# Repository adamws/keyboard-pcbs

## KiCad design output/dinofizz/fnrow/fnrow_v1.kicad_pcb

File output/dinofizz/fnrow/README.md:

## dinofizz/fnrow/fnrow_v1

[layout](fnrow_v1-kle.json) - [PCB](fnrow_v1.kicad_pcb)

{:loading="lazy"}

[Open in keyboard-layout-editor](http://www.keyboard-layout-editor.com/##@@_c=#777777;&=0,0&_x:1&c=#cccccc;&=0,1&=0,2&=0,3&=0,4&_x:0.5&c=#aaaaaa;&=0,5&=0,6&=1,0&=1,1&_x:0.5&c=#cccccc;&=1,2&=1,3&=1,4&=1,5)

{:loading="lazy"}

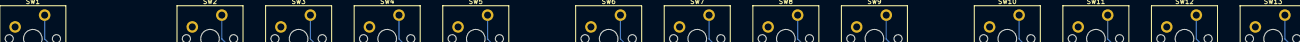
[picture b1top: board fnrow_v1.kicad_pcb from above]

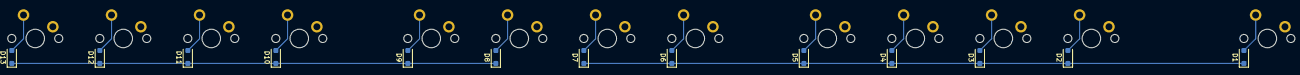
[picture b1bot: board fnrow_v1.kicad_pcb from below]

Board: 2 copper layers, 26 parts (13 on the bottom side), 21 nets.

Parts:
D1, D2, D3, D4, D5, D6, D7, D8, D9, D10, D11, D12, D13: D_SOD-123F
SW1, SW2, SW3, SW4, SW5, SW6, SW7, SW8, SW9, SW10, SW11, SW12, SW13: SW_Cherry_MX_PCB_1.00u

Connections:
COL0: SW1.1, SW8.1
COL1: SW2.1, SW9.1
COL2: SW3.1, SW10.1
COL3: SW4.1, SW11.1
COL4: SW5.1, SW12.1
COL5: SW6.1, SW13.1
unnamed: D1.2, SW1.2
unnamed: D2.2, SW2.2
unnamed: D3.2, SW3.2
unnamed: D4.2, SW4.2
unnamed: D5.2, SW5.2
unnamed: D6.2, SW6.2
unnamed: D7.2, SW7.2
unnamed: D8.2, SW8.2
unnamed: D9.2, SW9.2
unnamed: D10.2, SW10.2
unnamed: D11.2, SW11.2
unnamed: D12.2, SW12.2
unnamed: D13.2, SW13.2
ROW0: D1.1, D2.1, D3.1, D4.1, D5.1, D6.1, D7.1
ROW1: D8.1, D9.1, D10.1, D11.1, D12.1, D13.1

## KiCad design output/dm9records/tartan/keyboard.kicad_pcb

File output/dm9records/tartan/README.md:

## dm9records/tartan/keyboard

[layout](keyboard-kle.json) - [PCB](keyboard.kicad_pcb)

{:loading="lazy"}

[Open in keyboard-layout-editor](http://www.keyboard-layout-editor.com/##@@_x:2.5&c=#777777;&=0,0&_c=#cccccc;&=0,1&=0,2&=0,3&=0,4&=0,5&=0,6&=0,7&=0,8&=0,9&=0,10&=0,11&=0,12&_c=#aaaaaa&w:2;&=4,9%0A%0A%0A0,0;&@_x:2.5&w:1.5;&=1,0&_c=#cccccc;&=1,1&=1,2&=1,3&=1,4&=1,5&=1,6&=1,7&=1,8&=1,9&=1,10&=1,11&=1,12&_w:1.5;&=4,11%0A%0A%0A1,0;&@_x:2.5&c=#aaaaaa&w:1.75;&=2,0&_c=#cccccc;&=2,1&=2,2&=2,3&=2,4&=2,5&=2,6&=2,7&=2,8&=2,9&=2,10&=2,11&_c=#777777&w:2.25;&=2,12%0A%0A%0A1,0;&@_x:2.5&c=#aaaaaa&w:2.25;&=3,0%0A%0A%0A3,0&_c=#cccccc;&=3,2&=3,3&=3,4&=3,5&=3,6&=3,7&=3,8&=3,9&=3,10&=3,11&_c=#aaaaaa&w:2.75;&=3,12%0A%0A%0A2,0;&@_x:2.5&w:1.25;&=4,0&_w:1.25;&=4,1&_w:1.25;&=4,2&_c=#cccccc&w:6.25;&=4,3&_c=#aaaaaa&w:1.25;&=4,4&_w:1.25;&=4,5&_w:1.25;&=4,6&_w:1.25;&=4,7;&@_x:17.75&y:-5&c=#cccccc;&=4,11%0A%0A%0A0,1&_c=#aaaaaa;&=4,9%0A%0A%0A0,1;&@_x:18.75&c=#777777&w:1.25&h:2&w2:1.5&h2:1&x2:-0.25;&=2,12%0A%0A%0A1,1;&@_x:17.75&c=#cccccc;&=4,11%0A%0A%0A1,1;&@_c=#aaaaaa&w:1.25;&=3,0%0A%0A%0A3,1&_c=#cccccc;&=3,1%0A%0A%0A3,1&_x:15.5&c=#aaaaaa&w:1.75&w2:1;&=3,12%0A%0A%0A2,1&_c=#cccccc;&=4,12%0A%0A%0A2,1)

{:loading="lazy"}

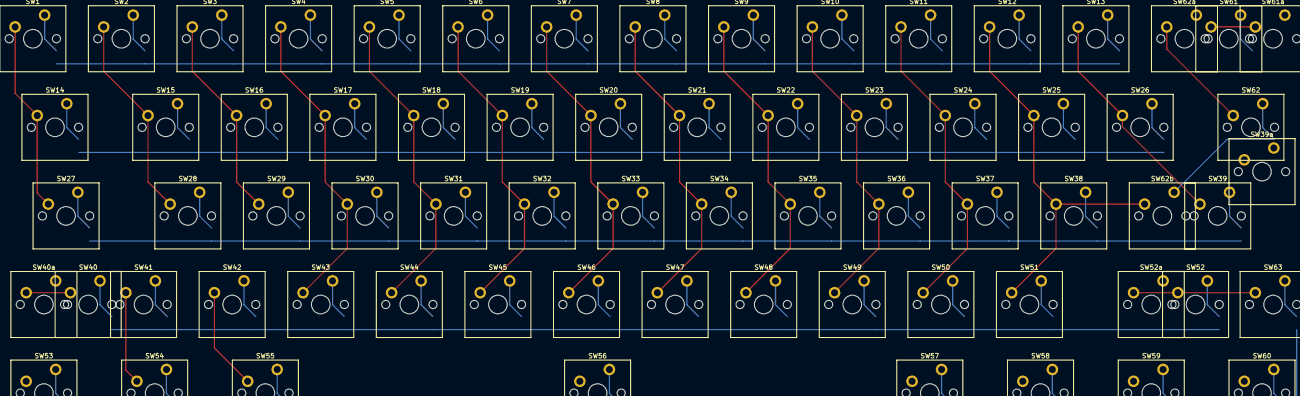
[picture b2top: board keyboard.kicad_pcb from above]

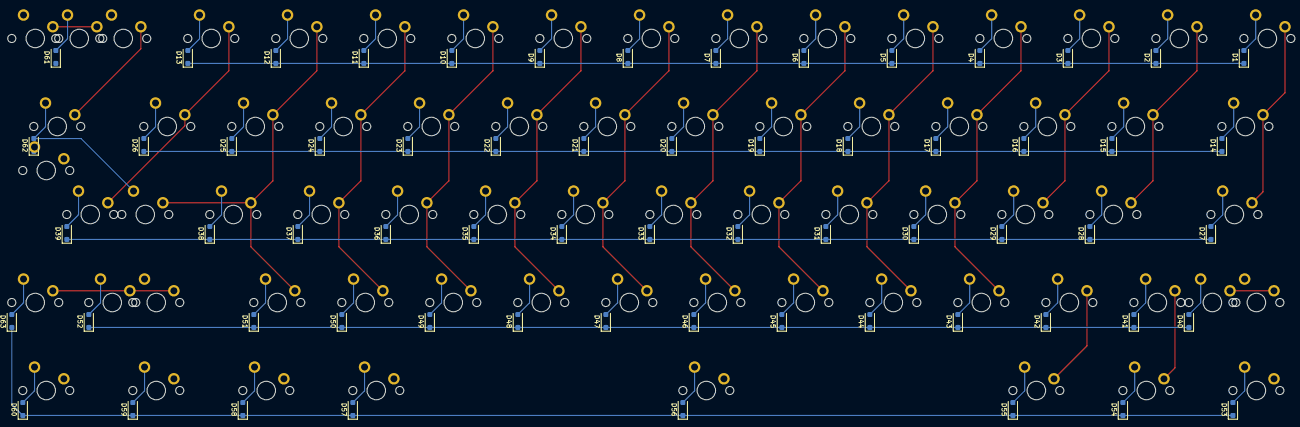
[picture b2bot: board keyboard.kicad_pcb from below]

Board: 2 copper layers, 132 parts (63 on the bottom side), 81 nets.

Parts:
D1, D2, D3, D4, D5, D6, D7, D8, D9, D10, D11, D12, D13, D14, D15, D16, D17, D18, D19, D20, D21, D22, D23, D24, D25, D26, D27, D28, D29, D30, D31, D32, D33, D34, D35, D36, D37, D38, D39, D40, D41, D42, D43, D44, D45, D46, D47, D48, D49, D50, D51, D52, D53, D54, D55, D56, D57, D58, D59, D60, D61, D62, D63: D_SOD-123F
SW1, SW2, SW3, SW4, SW5, SW6, SW7, SW8, SW9, SW10, SW11, SW12, SW13, SW14, SW15, SW16, SW17, SW18, SW19, SW20, SW21, SW22, SW23, SW24, SW25, SW26, SW27, SW28, SW29, SW30, SW31, SW32, SW33, SW34, SW35, SW36, SW37, SW38, SW39, SW39a, SW40, SW40a, SW41, SW42, SW43, SW44, SW45, SW46, SW47, SW48, SW49, SW50, SW51, SW52, SW52a, SW53, SW54, SW55, SW56, SW57, SW58, SW59, SW60, SW61, SW61a, SW62, SW62a, SW62b, SW63: SW_Cherry_MX_PCB_1.00u

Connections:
COL0: SW1.1, SW14.1, SW27.1, SW40.1, SW40a.1, SW53.1
COL1: SW2.1, SW15.1, SW28.1, SW41.1, SW54.1
COL2: SW3.1, SW16.1, SW29.1, SW42.1, SW55.1
COL3: SW4.1, SW17.1, SW30.1, SW43.1, SW56.1
COL4: SW5.1, SW18.1, SW31.1, SW44.1, SW57.1
COL5: SW6.1, SW19.1, SW32.1, SW45.1, SW58.1
COL6: SW7.1, SW20.1, SW33.1, SW46.1, SW59.1
COL7: SW8.1, SW21.1, SW34.1, SW47.1, SW60.1
COL8: SW9.1, SW22.1, SW35.1, SW48.1
COL9: SW10.1, SW23.1, SW36.1, SW49.1, SW61.1, SW61a.1
COL10: SW11.1, SW24.1, SW37.1, SW50.1
COL11: SW12.1, SW25.1, SW38.1, SW51.1, SW62.1, SW62a.1, SW62b.1
COL12: SW13.1, SW26.1, SW39.1, SW39a.1, SW52.1, SW52a.1, SW63.1
unnamed: D1.2, SW1.2
unnamed: D2.2, SW2.2
unnamed: D3.2, SW3.2
unnamed: D4.2, SW4.2
unnamed: D5.2, SW5.2
unnamed: D6.2, SW6.2
unnamed: D7.2, SW7.2
unnamed: D8.2, SW8.2
unnamed: D9.2, SW9.2
unnamed: D10.2, SW10.2
unnamed: D11.2, SW11.2
unnamed: D12.2, SW12.2
unnamed: D13.2, SW13.2
unnamed: D14.2, SW14.2
unnamed: D15.2, SW15.2
unnamed: D16.2, SW16.2
unnamed: D17.2, SW17.2
unnamed: D18.2, SW18.2
unnamed: D19.2, SW19.2
unnamed: D20.2, SW20.2
unnamed: D21.2, SW21.2
unnamed: D22.2, SW22.2
unnamed: D23.2, SW23.2
unnamed: D24.2, SW24.2
unnamed: D25.2, SW25.2
unnamed: D26.2, SW26.2
unnamed: D27.2, SW27.2
unnamed: D28.2, SW28.2
unnamed: D29.2, SW29.2
unnamed: D30.2, SW30.2
unnamed: D31.2, SW31.2
unnamed: D32.2, SW32.2
unnamed: D33.2, SW33.2
unnamed: D34.2, SW34.2
unnamed: D35.2, SW35.2
unnamed: D36.2, SW36.2
unnamed: D37.2, SW37.2
unnamed: D38.2, SW38.2
unnamed: D39.2, SW39.2, SW39a.2
unnamed: D40.2, SW40.2, SW40a.2
unnamed: D41.2, SW41.2
unnamed: D42.2, SW42.2
unnamed: D43.2, SW43.2
unnamed: D44.2, SW44.2
unnamed: D45.2, SW45.2
unnamed: D46.2, SW46.2
unnamed: D47.2, SW47.2
unnamed: D48.2, SW48.2
unnamed: D49.2, SW49.2
unnamed: D50.2, SW50.2
unnamed: D51.2, SW51.2
unnamed: D52.2, SW52.2, SW52a.2
unnamed: D53.2, SW53.2
unnamed: D54.2, SW54.2
unnamed: D55.2, SW55.2
unnamed: D56.2, SW56.2
unnamed: D57.2, SW57.2
unnamed: D58.2, SW58.2
unnamed: D59.2, SW59.2
unnamed: D60.2, SW60.2
unnamed: D61.2, SW61.2, SW61a.2
unnamed: D62.2, SW62.2, SW62a.2, SW62b.2
unnamed: D63.2, SW63.2
ROW0: D1.1, D2.1, D3.1, D4.1, D5.1, D6.1, D7.1, D8.1, D9.1, D10.1, D11.1, D12.1, D13.1
ROW1: D14.1, D15.1, D16.1, D17.1, D18.1, D19.1, D20.1, D21.1, D22.1, D23.1, D24.1, D25.1, D26.1
ROW2: D27.1, D28.1, D29.1, D30.1, D31.1, D32.1, D33.1, D34.1, D35.1, D36.1, D37.1, D38.1, D39.1
ROW3: D40.1, D41.1, D42.1, D43.1, D44.1, D45.1, D46.1, D47.1, D48.1, D49.1, D50.1, D51.1, D52.1
ROW4: D53.1, D54.1, D55.1, D56.1, D57.1, D58.1, D59.1, D60.1, D61.1, D62.1, D63.1

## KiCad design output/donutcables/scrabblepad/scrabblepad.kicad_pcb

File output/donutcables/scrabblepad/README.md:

## donutcables/scrabblepad

[layout](scrabblepad-kle.json) - [PCB](scrabblepad.kicad_pcb)

{:loading="lazy"}

[Open in keyboard-layout-editor](http://www.keyboard-layout-editor.com/##@@=0,0&=0,1&=0,2&=0,3&=0,4&=0,5&=0,6&=0,7&=0,8&=0,9&=0,10&=0,11&=0,12&=0,13&=0,14;&@=1,0&=1,1&=1,2&=1,3&=1,4&=1,5&=1,6&=1,7&=1,8&=1,9&=1,10&=1,11&=1,12&=1,13&=1,14;&@=2,0&=2,1&=2,2&=2,3&=2,4&=2,5&=2,6&=2,7&=2,8&=2,9&=2,10&=2,11&=2,12&=2,13&=2,14;&@=3,0&=3,1&=3,2&=3,3&=3,4&=3,5&=3,6&=3,7&=3,8&=3,9&=3,10&=3,11&=3,12&=3,13&=3,14;&@=4,0&=4,1&=4,2&=4,3&=4,4&=4,5&=4,6&=4,7&=4,8&=4,9&=4,10&=4,11&=4,12&=4,13&=4,14;&@=5,0&=5,1&=5,2&=5,3&=5,4&=5,5&=5,6&=5,7&=5,8&=5,9&=5,10&=5,11&=5,12&=5,13&=5,14;&@=6,0&=6,1&=6,2&=6,3&=6,4&=6,5&=6,6&=6,7&=6,8&=6,9&=6,10&=6,11&=6,12&=6,13&=6,14;&@=7,0&=7,1&=7,2&=7,3&=7,4&=7,5&=7,6&=7,7&=7,8&=7,9&=7,10&=7,11&=7,12&=7,13&=7,14;&@=8,0&=8,1&=8,2&=8,3&=8,4&=8,5&=8,6&=8,7&=8,8&=8,9&=8,10&=8,11&=8,12&=8,13&=8,14;&@=9,0&=9,1&=9,2&=9,3&=9,4&=9,5&=9,6&=9,7&=9,8&=9,9&=9,10&=9,11&=9,12&=9,13&=9,14;&@=10,0&=10,1&=10,2&=10,3&=10,4&=10,5&=10,6&=10,7&=10,8&=10,9&=10,10&=10,11&=10,12&=10,13&=10,14;&@=11,0&=11,1&=11,2&=11,3&=11,4&=11,5&=11,6&=11,7&=11,8&=11,9&=11,10&=11,11&=11,12&=11,13&=11,14;&@=12,0&=12,1&=12,2&=12,3&=12,4&=12,5&=12,6&=12,7&=12,8&=12,9&=12,10&=12,11&=12,12&=12,13&=12,14;&@=13,0&=13,1&=13,2&=13,3&=13,4&=13,5&=13,6&=13,7&=13,8&=13,9&=13,10&=13,11&=13,12&=13,13&=13,14;&@=14,0&=14,1&=14,2&=14,3&=14,4&=14,5&=14,6&=14,7&=14,8&=14,9&=14,10&=14,11&=14,12&=14,13&=14,14)

{:loading="lazy"}

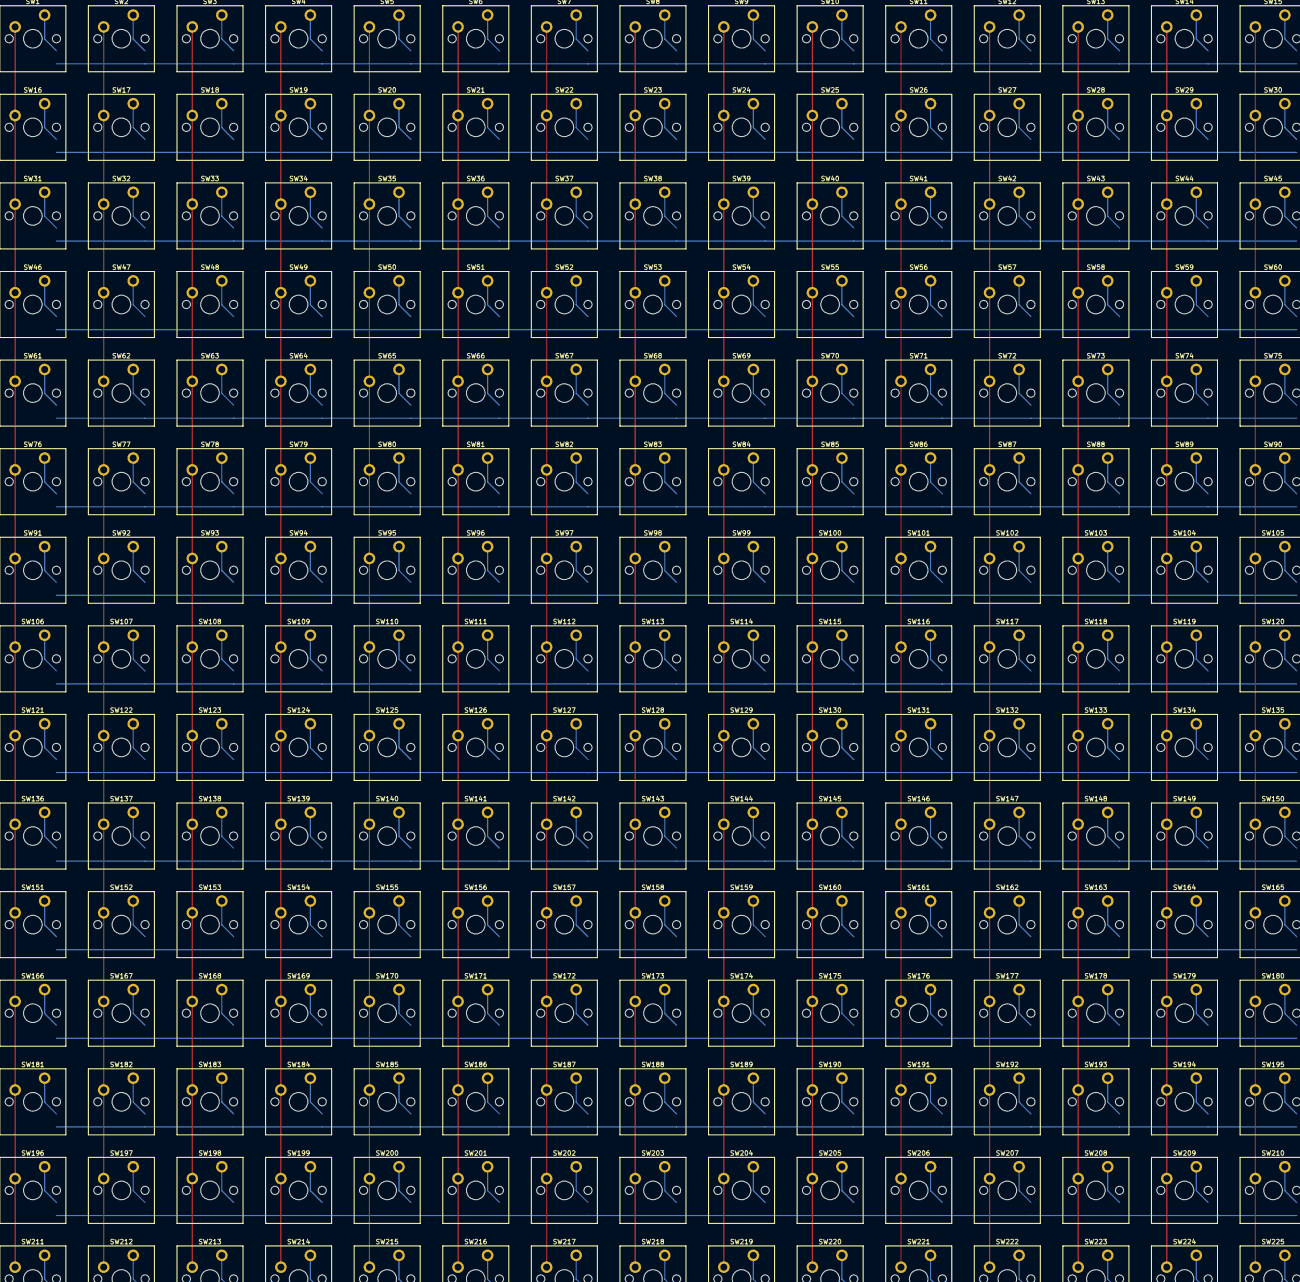
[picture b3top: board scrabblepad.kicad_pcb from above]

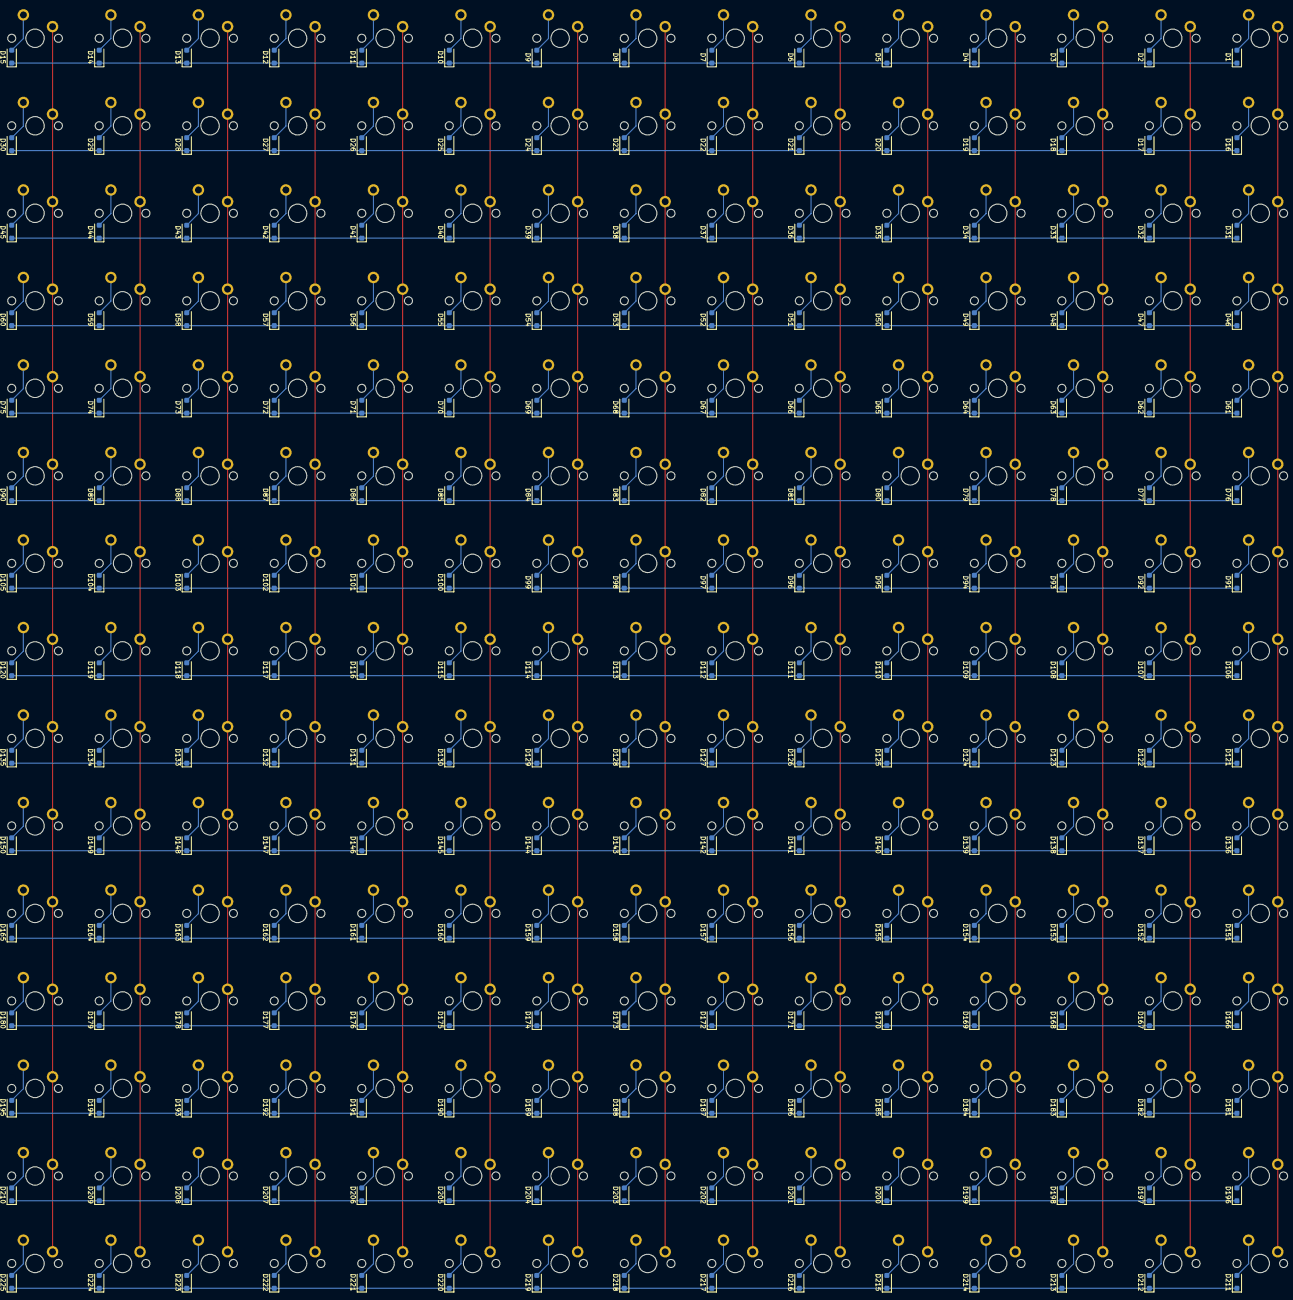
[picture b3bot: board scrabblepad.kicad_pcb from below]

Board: 2 copper layers, 450 parts (225 on the bottom side), 255 nets.

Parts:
D1, D2, D3, D4, D5, D6, D7, D8, D9, D10, D11, D12, D13, D14, D15, D16, D17, D18, D19, D20, D21, D22, D23, D24, D25, D26, D27, D28, D29, D30, D31, D32, D33, D34, D35, D36, D37, D38, D39, D40, D41, D42, D43, D44, D45, D46, D47, D48, D49, D50, D51, D52, D53, D54, D55, D56, D57, D58, D59, D60, D61, D62, D63, D64, D65, D66, D67, D68, D69, D70, D71, D72, D73, D74, D75, D76, D77, D78, D79, D80, D81, D82, D83, D84, D85, D86, D87, D88, D89, D90, D91, D92, D93, D94, D95, D96, D97, D98, D99, D100, D101, D102, D103, D104, D105, D106, D107, D108, D109, D110, D111, D112, D113, D114, D115, D116, D117, D118, D119, D120, D121, D122, D123, D124, D125, D126, D127, D128, D129, D130, D131, D132, D133, D134, D135, D136, D137, D138, D139, D140, D141, D142, D143, D144, D145, D146, D147, D148, D149, D150, D151, D152, D153, D154, D155, D156, D157, D158, D159, D160, D161, D162, D163, D164, D165, D166, D167, D168, D169, D170, D171, D172, D173, D174, D175, D176, D177, D178, D179, D180, D181, D182, D183, D184, D185, D186, D187, D188, D189, D190, D191, D192, D193, D194, D195, D196, D197, D198, D199, D200, D201, D202, D203, D204, D205, D206, D207, D208, D209, D210, D211, D212, D213, D214, D215, D216, D217, D218, D219, D220, D221, D222, D223, D224, D225: D_SOD-123F
SW1, SW2, SW3, SW4, SW5, SW6, SW7, SW8, SW9, SW10, SW11, SW12, SW13, SW14, SW15, SW16, SW17, SW18, SW19, SW20, SW21, SW22, SW23, SW24, SW25, SW26, SW27, SW28, SW29, SW30, SW31, SW32, SW33, SW34, SW35, SW36, SW37, SW38, SW39, SW40, SW41, SW42, SW43, SW44, SW45, SW46, SW47, SW48, SW49, SW50, SW51, SW52, SW53, SW54, SW55, SW56, SW57, SW58, SW59, SW60, SW61, SW62, SW63, SW64, SW65, SW66, SW67, SW68, SW69, SW70, SW71, SW72, SW73, SW74, SW75, SW76, SW77, SW78, SW79, SW80, SW81, SW82, SW83, SW84, SW85, SW86, SW87, SW88, SW89, SW90, SW91, SW92, SW93, SW94, SW95, SW96, SW97, SW98, SW99, SW100, SW101, SW102, SW103, SW104, SW105, SW106, SW107, SW108, SW109, SW110, SW111, SW112, SW113, SW114, SW115, SW116, SW117, SW118, SW119, SW120, SW121, SW122, SW123, SW124, SW125, SW126, SW127, SW128, SW129, SW130, SW131, SW132, SW133, SW134, SW135, SW136, SW137, SW138, SW139, SW140, SW141, SW142, SW143, SW144, SW145, SW146, SW147, SW148, SW149, SW150, SW151, SW152, SW153, SW154, SW155, SW156, SW157, SW158, SW159, SW160, SW161, SW162, SW163, SW164, SW165, SW166, SW167, SW168, SW169, SW170, SW171, SW172, SW173, SW174, SW175, SW176, SW177, SW178, SW179, SW180, SW181, SW182, SW183, SW184, SW185, SW186, SW187, SW188, SW189, SW190, SW191, SW192, SW193, SW194, SW195, SW196, SW197, SW198, SW199, SW200, SW201, SW202, SW203, SW204, SW205, SW206, SW207, SW208, SW209, SW210, SW211, SW212, SW213, SW214, SW215, SW216, SW217, SW218, SW219, SW220, SW221, SW222, SW223, SW224, SW225: SW_Cherry_MX_PCB_1.00u

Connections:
COL0: SW1.1, SW16.1, SW31.1, SW46.1, SW61.1, SW76.1, SW91.1, SW106.1, SW121.1, SW136.1, SW151.1, SW166.1, SW181.1, SW196.1, SW211.1
COL1: SW2.1, SW17.1, SW32.1, SW47.1, SW62.1, SW77.1, SW92.1, SW107.1, SW122.1, SW137.1, SW152.1, SW167.1, SW182.1, SW197.1, SW212.1
COL2: SW3.1, SW18.1, SW33.1, SW48.1, SW63.1, SW78.1, SW93.1, SW108.1, SW123.1, SW138.1, SW153.1, SW168.1, SW183.1, SW198.1, SW213.1
COL3: SW4.1, SW19.1, SW34.1, SW49.1, SW64.1, SW79.1, SW94.1, SW109.1, SW124.1, SW139.1, SW154.1, SW169.1, SW184.1, SW199.1, SW214.1
COL4: SW5.1, SW20.1, SW35.1, SW50.1, SW65.1, SW80.1, SW95.1, SW110.1, SW125.1, SW140.1, SW155.1, SW170.1, SW185.1, SW200.1, SW215.1
COL5: SW6.1, SW21.1, SW36.1, SW51.1, SW66.1, SW81.1, SW96.1, SW111.1, SW126.1, SW141.1, SW156.1, SW171.1, SW186.1, SW201.1, SW216.1
COL6: SW7.1, SW22.1, SW37.1, SW52.1, SW67.1, SW82.1, SW97.1, SW112.1, SW127.1, SW142.1, SW157.1, SW172.1, SW187.1, SW202.1, SW217.1
COL7: SW8.1, SW23.1, SW38.1, SW53.1, SW68.1, SW83.1, SW98.1, SW113.1, SW128.1, SW143.1, SW158.1, SW173.1, SW188.1, SW203.1, SW218.1
COL8: SW9.1, SW24.1, SW39.1, SW54.1, SW69.1, SW84.1, SW99.1, SW114.1, SW129.1, SW144.1, SW159.1, SW174.1, SW189.1, SW204.1, SW219.1
COL9: SW10.1, SW25.1, SW40.1, SW55.1, SW70.1, SW85.1, SW100.1, SW115.1, SW130.1, SW145.1, SW160.1, SW175.1, SW190.1, SW205.1, SW220.1
COL10: SW11.1, SW26.1, SW41.1, SW56.1, SW71.1, SW86.1, SW101.1, SW116.1, SW131.1, SW146.1, SW161.1, SW176.1, SW191.1, SW206.1, SW221.1
COL11: SW12.1, SW27.1, SW42.1, SW57.1, SW72.1, SW87.1, SW102.1, SW117.1, SW132.1, SW147.1, SW162.1, SW177.1, SW192.1, SW207.1, SW222.1
COL12: SW13.1, SW28.1, SW43.1, SW58.1, SW73.1, SW88.1, SW103.1, SW118.1, SW133.1, SW148.1, SW163.1, SW178.1, SW193.1, SW208.1, SW223.1
COL13: SW14.1, SW29.1, SW44.1, SW59.1, SW74.1, SW89.1, SW104.1, SW119.1, SW134.1, SW149.1, SW164.1, SW179.1, SW194.1, SW209.1, SW224.1
COL14: SW15.1, SW30.1, SW45.1, SW60.1, SW75.1, SW90.1, SW105.1, SW120.1, SW135.1, SW150.1, SW165.1, SW180.1, SW195.1, SW210.1, SW225.1
unnamed: D1.2, SW1.2
unnamed: D2.2, SW2.2
unnamed: D3.2, SW3.2
unnamed: D4.2, SW4.2
unnamed: D5.2, SW5.2
unnamed: D6.2, SW6.2
unnamed: D7.2, SW7.2
unnamed: D8.2, SW8.2
unnamed: D9.2, SW9.2
unnamed: D10.2, SW10.2
unnamed: D11.2, SW11.2
unnamed: D12.2, SW12.2
unnamed: D13.2, SW13.2
unnamed: D14.2, SW14.2
unnamed: D15.2, SW15.2
unnamed: D16.2, SW16.2
unnamed: D17.2, SW17.2
unnamed: D18.2, SW18.2
unnamed: D19.2, SW19.2
unnamed: D20.2, SW20.2
unnamed: D21.2, SW21.2
unnamed: D22.2, SW22.2
unnamed: D23.2, SW23.2
unnamed: D24.2, SW24.2
unnamed: D25.2, SW25.2
unnamed: D26.2, SW26.2
unnamed: D27.2, SW27.2
unnamed: D28.2, SW28.2
unnamed: D29.2, SW29.2
unnamed: D30.2, SW30.2
unnamed: D31.2, SW31.2
unnamed: D32.2, SW32.2
unnamed: D33.2, SW33.2
unnamed: D34.2, SW34.2
unnamed: D35.2, SW35.2
unnamed: D36.2, SW36.2
unnamed: D37.2, SW37.2
unnamed: D38.2, SW38.2
unnamed: D39.2, SW39.2
unnamed: D40.2, SW40.2
unnamed: D41.2, SW41.2
unnamed: D42.2, SW42.2
unnamed: D43.2, SW43.2
unnamed: D44.2, SW44.2
unnamed: D45.2, SW45.2
unnamed: D46.2, SW46.2
unnamed: D47.2, SW47.2
unnamed: D48.2, SW48.2
unnamed: D49.2, SW49.2
unnamed: D50.2, SW50.2
unnamed: D51.2, SW51.2
unnamed: D52.2, SW52.2
unnamed: D53.2, SW53.2
unnamed: D54.2, SW54.2
unnamed: D55.2, SW55.2
unnamed: D56.2, SW56.2
unnamed: D57.2, SW57.2
unnamed: D58.2, SW58.2
unnamed: D59.2, SW59.2
unnamed: D60.2, SW60.2
unnamed: D61.2, SW61.2
unnamed: D62.2, SW62.2
unnamed: D63.2, SW63.2
unnamed: D64.2, SW64.2
unnamed: D65.2, SW65.2
unnamed: D66.2, SW66.2
unnamed: D67.2, SW67.2
unnamed: D68.2, SW68.2
unnamed: D69.2, SW69.2
unnamed: D70.2, SW70.2
unnamed: D71.2, SW71.2
unnamed: D72.2, SW72.2
unnamed: D73.2, SW73.2
unnamed: D74.2, SW74.2
unnamed: D75.2, SW75.2
unnamed: D76.2, SW76.2
unnamed: D77.2, SW77.2
unnamed: D78.2, SW78.2
unnamed: D79.2, SW79.2
unnamed: D80.2, SW80.2
unnamed: D81.2, SW81.2
unnamed: D82.2, SW82.2
unnamed: D83.2, SW83.2
unnamed: D84.2, SW84.2
unnamed: D85.2, SW85.2
unnamed: D86.2, SW86.2
unnamed: D87.2, SW87.2
unnamed: D88.2, SW88.2
unnamed: D89.2, SW89.2
unnamed: D90.2, SW90.2
unnamed: D91.2, SW91.2
unnamed: D92.2, SW92.2
unnamed: D93.2, SW93.2
unnamed: D94.2, SW94.2
unnamed: D95.2, SW95.2
unnamed: D96.2, SW96.2
unnamed: D97.2, SW97.2
unnamed: D98.2, SW98.2
unnamed: D99.2, SW99.2
unnamed: D100.2, SW100.2
unnamed: D101.2, SW101.2
unnamed: D102.2, SW102.2
unnamed: D103.2, SW103.2
unnamed: D104.2, SW104.2
unnamed: D105.2, SW105.2
unnamed: D106.2, SW106.2
unnamed: D107.2, SW107.2
unnamed: D108.2, SW108.2
unnamed: D109.2, SW109.2
unnamed: D110.2, SW110.2
unnamed: D111.2, SW111.2
unnamed: D112.2, SW112.2
unnamed: D113.2, SW113.2
unnamed: D114.2, SW114.2
unnamed: D115.2, SW115.2
unnamed: D116.2, SW116.2
unnamed: D117.2, SW117.2
unnamed: D118.2, SW118.2
unnamed: D119.2, SW119.2
unnamed: D120.2, SW120.2
unnamed: D121.2, SW121.2
unnamed: D122.2, SW122.2
unnamed: D123.2, SW123.2
unnamed: D124.2, SW124.2
unnamed: D125.2, SW125.2
unnamed: D126.2, SW126.2
unnamed: D127.2, SW127.2
unnamed: D128.2, SW128.2
unnamed: D129.2, SW129.2
unnamed: D130.2, SW130.2
unnamed: D131.2, SW131.2
unnamed: D132.2, SW132.2
unnamed: D133.2, SW133.2
unnamed: D134.2, SW134.2
unnamed: D135.2, SW135.2
unnamed: D136.2, SW136.2
unnamed: D137.2, SW137.2
unnamed: D138.2, SW138.2
unnamed: D139.2, SW139.2
unnamed: D140.2, SW140.2
unnamed: D141.2, SW141.2
unnamed: D142.2, SW142.2
unnamed: D143.2, SW143.2
unnamed: D144.2, SW144.2
unnamed: D145.2, SW145.2
unnamed: D146.2, SW146.2
unnamed: D147.2, SW147.2
unnamed: D148.2, SW148.2
unnamed: D149.2, SW149.2
unnamed: D150.2, SW150.2
unnamed: D151.2, SW151.2
unnamed: D152.2, SW152.2
unnamed: D153.2, SW153.2
unnamed: D154.2, SW154.2
unnamed: D155.2, SW155.2
unnamed: D156.2, SW156.2
unnamed: D157.2, SW157.2
unnamed: D158.2, SW158.2
unnamed: D159.2, SW159.2
unnamed: D160.2, SW160.2
unnamed: D161.2, SW161.2
unnamed: D162.2, SW162.2
unnamed: D163.2, SW163.2
unnamed: D164.2, SW164.2
unnamed: D165.2, SW165.2
unnamed: D166.2, SW166.2
unnamed: D167.2, SW167.2
unnamed: D168.2, SW168.2
unnamed: D169.2, SW169.2
unnamed: D170.2, SW170.2
unnamed: D171.2, SW171.2
unnamed: D172.2, SW172.2
unnamed: D173.2, SW173.2
unnamed: D174.2, SW174.2
unnamed: D175.2, SW175.2
unnamed: D176.2, SW176.2
unnamed: D177.2, SW177.2
unnamed: D178.2, SW178.2
unnamed: D179.2, SW179.2
unnamed: D180.2, SW180.2
unnamed: D181.2, SW181.2
unnamed: D182.2, SW182.2
unnamed: D183.2, SW183.2
unnamed: D184.2, SW184.2
unnamed: D185.2, SW185.2
unnamed: D186.2, SW186.2
unnamed: D187.2, SW187.2
unnamed: D188.2, SW188.2
unnamed: D189.2, SW189.2
unnamed: D190.2, SW190.2
unnamed: D191.2, SW191.2
unnamed: D192.2, SW192.2
unnamed: D193.2, SW193.2
unnamed: D194.2, SW194.2
unnamed: D195.2, SW195.2
unnamed: D196.2, SW196.2
unnamed: D197.2, SW197.2
unnamed: D198.2, SW198.2
unnamed: D199.2, SW199.2
unnamed: D200.2, SW200.2
unnamed: D201.2, SW201.2
unnamed: D202.2, SW202.2
unnamed: D203.2, SW203.2
unnamed: D204.2, SW204.2
unnamed: D205.2, SW205.2
unnamed: D206.2, SW206.2
unnamed: D207.2, SW207.2
unnamed: D208.2, SW208.2
unnamed: D209.2, SW209.2
unnamed: D210.2, SW210.2
unnamed: D211.2, SW211.2
unnamed: D212.2, SW212.2
unnamed: D213.2, SW213.2
unnamed: D214.2, SW214.2
unnamed: D215.2, SW215.2
unnamed: D216.2, SW216.2
unnamed: D217.2, SW217.2
unnamed: D218.2, SW218.2
unnamed: D219.2, SW219.2
unnamed: D220.2, SW220.2
unnamed: D221.2, SW221.2
unnamed: D222.2, SW222.2
unnamed: D223.2, SW223.2
unnamed: D224.2, SW224.2
unnamed: D225.2, SW225.2
ROW0: D1.1, D2.1, D3.1, D4.1, D5.1, D6.1, D7.1, D8.1, D9.1, D10.1, D11.1, D12.1, D13.1, D14.1, D15.1
ROW1: D16.1, D17.1, D18.1, D19.1, D20.1, D21.1, D22.1, D23.1, D24.1, D25.1, D26.1, D27.1, D28.1, D29.1, D30.1
ROW2: D31.1, D32.1, D33.1, D34.1, D35.1, D36.1, D37.1, D38.1, D39.1, D40.1, D41.1, D42.1, D43.1, D44.1, D45.1
ROW3: D46.1, D47.1, D48.1, D49.1, D50.1, D51.1, D52.1, D53.1, D54.1, D55.1, D56.1, D57.1, D58.1, D59.1, D60.1
ROW4: D61.1, D62.1, D63.1, D64.1, D65.1, D66.1, D67.1, D68.1, D69.1, D70.1, D71.1, D72.1, D73.1, D74.1, D75.1
ROW5: D76.1, D77.1, D78.1, D79.1, D80.1, D81.1, D82.1, D83.1, D84.1, D85.1, D86.1, D87.1, D88.1, D89.1, D90.1
ROW6: D91.1, D92.1, D93.1, D94.1, D95.1, D96.1, D97.1, D98.1, D99.1, D100.1, D101.1, D102.1, D103.1, D104.1, D105.1
ROW7: D106.1, D107.1, D108.1, D109.1, D110.1, D111.1, D112.1, D113.1, D114.1, D115.1, D116.1, D117.1, D118.1, D119.1, D120.1
ROW8: D121.1, D122.1, D123.1, D124.1, D125.1, D126.1, D127.1, D128.1, D129.1, D130.1, D131.1, D132.1, D133.1, D134.1, D135.1
ROW9: D136.1, D137.1, D138.1, D139.1, D140.1, D141.1, D142.1, D143.1, D144.1, D145.1, D146.1, D147.1, D148.1, D149.1, D150.1
ROW10: D151.1, D152.1, D153.1, D154.1, D155.1, D156.1, D157.1, D158.1, D159.1, D160.1, D161.1, D162.1, D163.1, D164.1, D165.1
ROW11: D166.1, D167.1, D168.1, D169.1, D170.1, D171.1, D172.1, D173.1, D174.1, D175.1, D176.1, D177.1, D178.1, D179.1, D180.1
ROW12: D181.1, D182.1, D183.1, D184.1, D185.1, D186.1, D187.1, D188.1, D189.1, D190.1, D191.1, D192.1, D193.1, D194.1, D195.1
ROW13: D196.1, D197.1, D198.1, D199.1, D200.1, D201.1, D202.1, D203.1, D204.1, D205.1, D206.1, D207.1, D208.1, D209.1, D210.1
ROW14: D211.1, D212.1, D213.1, D214.1, D215.1, D216.1, D217.1, D218.1, D219.1, D220.1, D221.1, D222.1, D223.1, D224.1, D225.1
